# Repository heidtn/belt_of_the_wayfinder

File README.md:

# belt of the wayfinder
This project is the design for a belt that uses vibrational motors to tell the wearer where north is.  This has been inspired by many similar projects in the past.  The basic concept is that by always knowing north, the wearer can gain an intuitive understanding of where north is and improve their sense of direction.

This project includes the PCB design, firmware, and mechanical assemblies.

CAD has been designed using Onshape and the link can be found [here](https://cad.onshape.com/documents/3174cd1b7d359cff45b60529/w/59155bcb796c6976c8cc7d48/e/c52ae8d364edc915756cc2c3)

As of this commit, the firmware and hardware have not yet been tested and development is still underway.

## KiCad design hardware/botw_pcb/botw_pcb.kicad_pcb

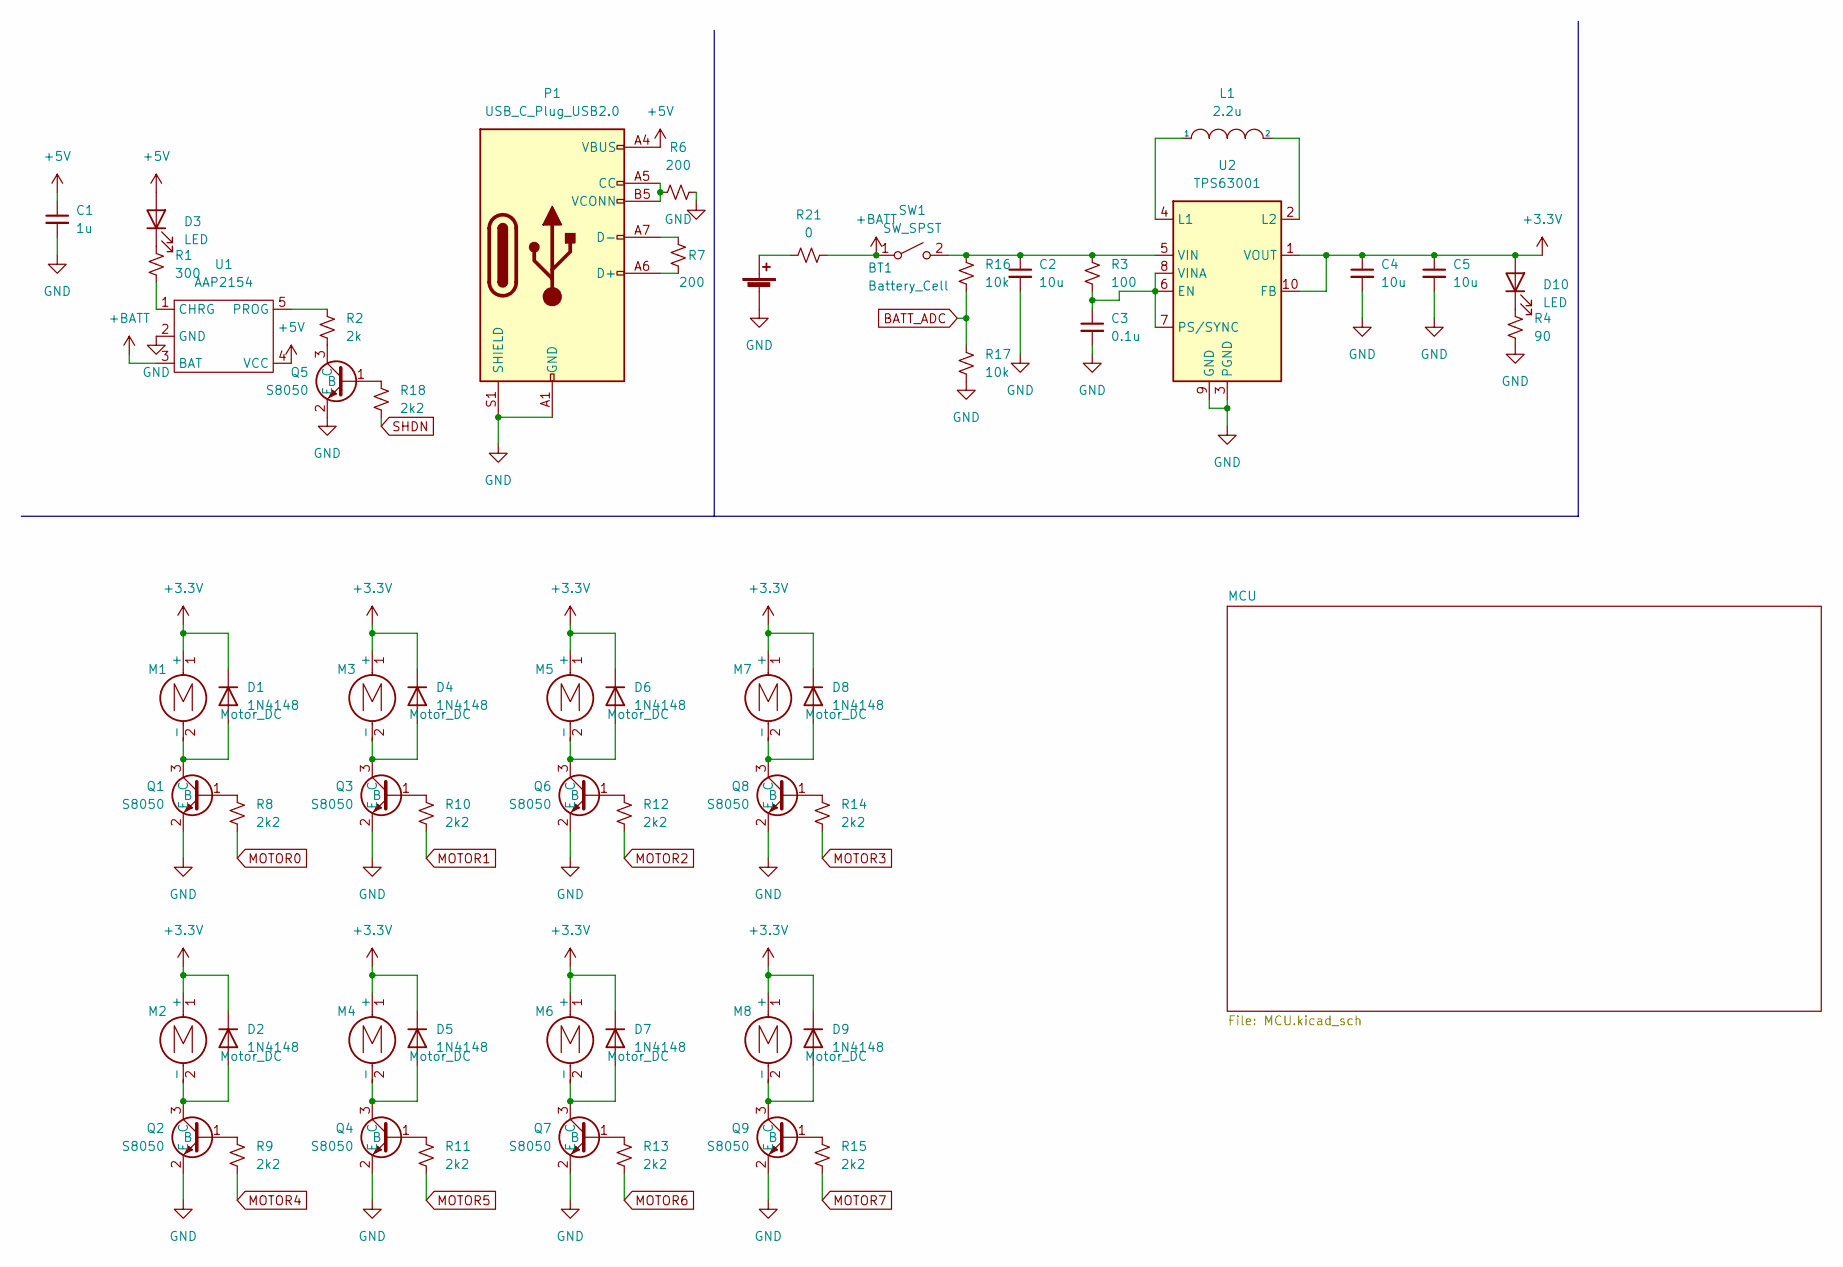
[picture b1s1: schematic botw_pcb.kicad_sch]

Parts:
BT1: Battery_Cell; PinHeader_1x02_P2.54mm_Vertical
C1: 1u; C_0603_1608Metric
C2, C4, C5: 10u; C_0603_1608Metric
C3: 0.1u; C_0603_1608Metric
D1, D2, D4, D5, D6, D7, D8, D9: 1N4148; D_SOD-123
D3, D10: LED; LED_0603_1608Metric
L1: 2.2u; L_0805_2012Metric
M1, M2, M3, M4, M5, M6, M7, M8: Motor_DC; PinHeader_1x02_P2.54mm_Vertical
P1: USB_C_Plug_USB2.0; USB_C_Receptacle_HRO_TYPE-C-31-M-12
Q1, Q2, Q3, Q4, Q5, Q6, Q7, Q8, Q9: S8050; SOT-23
R1: 300; R_0603_1608Metric
R2: 2k; R_0603_1608Metric
R3: 100; R_0603_1608Metric
R4: 90; R_0603_1608Metric
R6, R7: 200; R_0603_1608Metric
R8, R9, R10, R11, R12, R13, R14, R15, R18: 2k2; R_0603_1608Metric
R16, R17: 10k; R_0603_1608Metric
R21: 0; R_0603_1608Metric
SW1: SW_SPST; PinSocket_1x02_P2.54mm_Vertical
U1: AAP2154; TSOT-25
U2: TPS63001; Texas_DRC0010J_ThermalVias

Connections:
+3.3V: C4.1, C5.1, D1.1 (K), D2.1 (K), D4.1 (K), D5.1 (K), D6.1 (K), D7.1 (K), D8.1 (K), D9.1 (K), D10.2 (A), M1.1 (+), M2.1 (+), M3.1 (+), M4.1 (+), M5.1 (+), M6.1 (+), M7.1 (+), M8.1 (+), U2.1 (VOUT), U2.10 (FB); also elsewhere on the board
+5V: C1.1, D3.2 (A), P1.A4 (VBUS), P1.A9 (VBUS), P1.B4 (VBUS), P1.B9 (VBUS), U1.4 (VCC)
+BATT: R21.2, SW1.1 (A), U1.3 (BAT)
BATT_ADC: R16.2, R17.1; also elsewhere on the board
GND: BT1.2 (-), C1.2, C2.2, C3.2, C4.2, C5.2, P1.A1 (GND), P1.A12 (GND), P1.B1 (GND), P1.B12 (GND), P1.S1 (SHIELD), Q1.2 (E), Q2.2 (E), Q3.2 (E), Q4.2 (E), Q5.2 (E), Q6.2 (E), Q7.2 (E), Q8.2 (E), Q9.2 (E), R4.2, R6.2, R17.2, U1.2 (GND), U2.3 (PGND), U2.9 (GND), U2.11 (PGND); also elsewhere on the board
MOTOR0: R8.2; also elsewhere on the board
MOTOR1: R10.2; also elsewhere on the board
MOTOR2: R12.2; also elsewhere on the board
MOTOR3: R14.2; also elsewhere on the board
MOTOR4: R9.2; also elsewhere on the board
MOTOR5: R11.2; also elsewhere on the board
MOTOR6: R13.2; also elsewhere on the board
MOTOR7: R15.2; also elsewhere on the board
unnamed: BT1.1 (+), R21.1
unnamed: C2.1, R3.1, R16.1, SW1.2 (B), U2.5 (VIN)
unnamed: C3.1, R3.2, U2.6 (EN), U2.7 (PS/SYNC), U2.8 (VINA)
unnamed: D1.2 (A), M1.2 (-), Q1.3 (C)
unnamed: D2.2 (A), M2.2 (-), Q2.3 (C)
unnamed: D3.1 (K), R1.1
unnamed: D4.2 (A), M3.2 (-), Q3.3 (C)
unnamed: D5.2 (A), M4.2 (-), Q4.3 (C)
unnamed: D6.2 (A), M5.2 (-), Q6.3 (C)
unnamed: D7.2 (A), M6.2 (-), Q7.3 (C)
unnamed: D8.2 (A), M7.2 (-), Q8.3 (C)
unnamed: D9.2 (A), M8.2 (-), Q9.3 (C)
unnamed: D10.1 (K), R4.1
unnamed: L1.1, U2.4 (L1)
unnamed: L1.2, U2.2 (L2)
unnamed: P1.A5 (CC), P1.B5 (VCONN), R6.1
unnamed: P1.A6 (D+), R7.2
unnamed: P1.A7 (D-), R7.1
unnamed: R1.2, U1.1 (CHRG)
unnamed: R2.1, U1.5 (PROG)
unnamed: Q5.3 (C), R2.2
unnamed: Q1.1 (B), R8.1
unnamed: Q2.1 (B), R9.1
unnamed: Q3.1 (B), R10.1
unnamed: Q4.1 (B), R11.1
unnamed: Q6.1 (B), R12.1
unnamed: Q7.1 (B), R13.1
unnamed: Q8.1 (B), R14.1
unnamed: Q9.1 (B), R15.1
unnamed: Q5.1 (B), R18.1
SHDN: R18.2; also elsewhere on the board

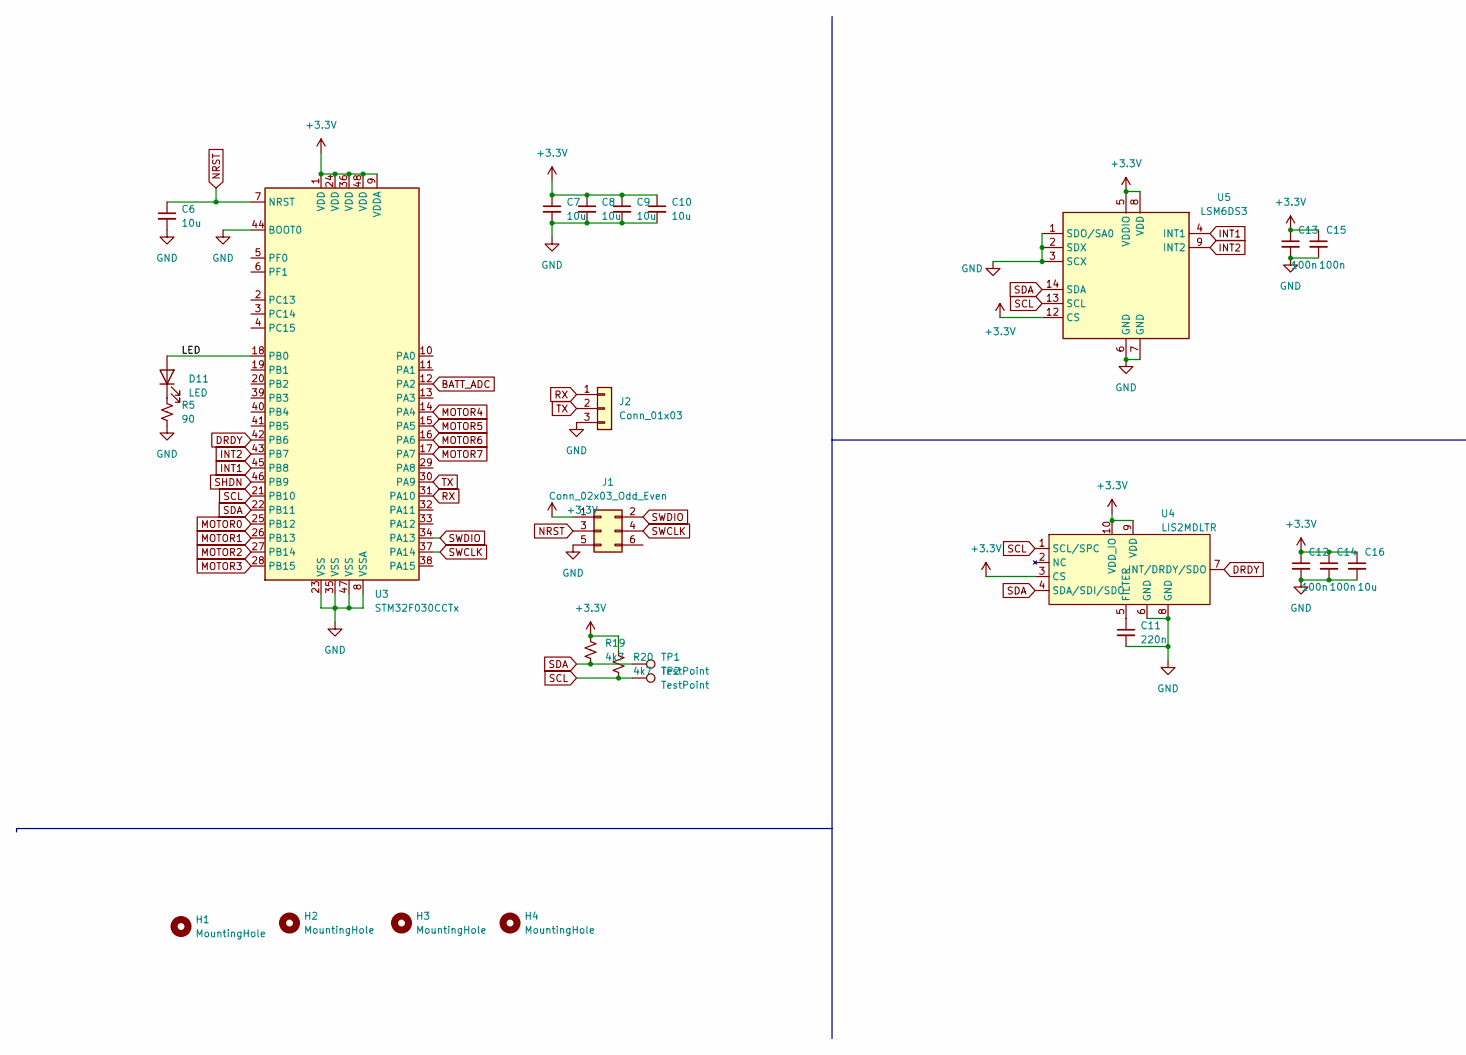
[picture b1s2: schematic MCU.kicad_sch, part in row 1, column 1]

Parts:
C6, C7, C8, C9, C10, C16: 10u; C_0603_1608Metric
C11: 220n; C_0603_1608Metric
C12, C13, C14, C15: 100n; C_0603_1608Metric
D11: LED; LED_0603_1608Metric
H1, H2, H3, H4: MountingHole; MountingHole_2.7mm_M2.5
J1: Conn_02x03_Odd_Even; Tag-Connect_TC2030-IDC-FP_2x03_P1.27mm_Vertical
J2: Conn_01x03; PinHeader_1x03_P2.54mm_Vertical
R5: 90; R_0603_1608Metric
R19, R20: 4k7; R_0603_1608Metric
TP1, TP2: TestPoint; TestPoint_Pad_D1.0mm
U3: STM32F030CCTx; LQFP-48_7x7mm_P0.5mm
U4: LIS2MDLTR; LGA-12_2x2mm_P0.5mm
U5: LSM6DS3; LGA-14_3x2.5mm_P0.5mm_LayoutBorder3x4y

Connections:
+3.3V: C7.1, C8.1, C9.1, C10.1, C12.1, C13.1, C14.1, C15.1, C16.1, J1.1, R19.1, R20.1, U3.1 (VDD), U3.9 (VDDA), U3.24 (VDD), U3.36 (VDD), U3.48 (VDD), U4.3 (CS), U4.9 (VDD), U4.10 (VDD_IO), U5.5 (VDDIO), U5.8 (VDD), U5.12 (CS); also elsewhere on the board
/MCU/LED: D11.2 (A), U3.18 (PB0)
BATT_ADC: U3.12 (PA2); also elsewhere on the board
DRDY: U3.42 (PB6), U4.7 (INT/DRDY/SDO)
GND: C6.2, C7.2, C8.2, C9.2, C10.2, C11.2, C12.2, C13.2, C14.2, C15.2, C16.2, J1.5, J2.3, R5.2, U3.8 (VSSA), U3.23 (VSS), U3.35 (VSS), U3.44 (BOOT0), U3.47 (VSS), U4.6 (GND), U4.8 (GND), U5.1 (SDO/SA0), U5.2 (SDX), U5.3 (SCX), U5.6 (GND), U5.7 (GND); also elsewhere on the board
INT1: U3.45 (PB8), U5.4 (INT1)
INT2: U3.43 (PB7), U5.9 (INT2)
MOTOR0: U3.25 (PB12); also elsewhere on the board
MOTOR1: U3.26 (PB13); also elsewhere on the board
MOTOR2: U3.27 (PB14); also elsewhere on the board
MOTOR3: U3.28 (PB15); also elsewhere on the board
MOTOR4: U3.14 (PA4); also elsewhere on the board
MOTOR5: U3.15 (PA5); also elsewhere on the board
MOTOR6: U3.16 (PA6); also elsewhere on the board
MOTOR7: U3.17 (PA7); also elsewhere on the board
NRST: C6.1, J1.3, U3.7 (NRST)
unnamed: C11.1, U4.5 (FILTER)
unnamed: D11.1 (K), R5.1
RX: J2.1, U3.31 (PA10)
SCL: R20.2, TP2.1, U3.21 (PB10), U4.1 (SCL/SPC), U5.13 (SCL)
SDA: R19.2, TP1.1, U3.22 (PB11), U4.4 (SDA/SDI/SDO), U5.14 (SDA)
SHDN: U3.46 (PB9); also elsewhere on the board
SWCLK: J1.4, U3.37 (PA14)
SWDIO: J1.2, U3.34 (PA13)
TX: J2.2, U3.30 (PA9)

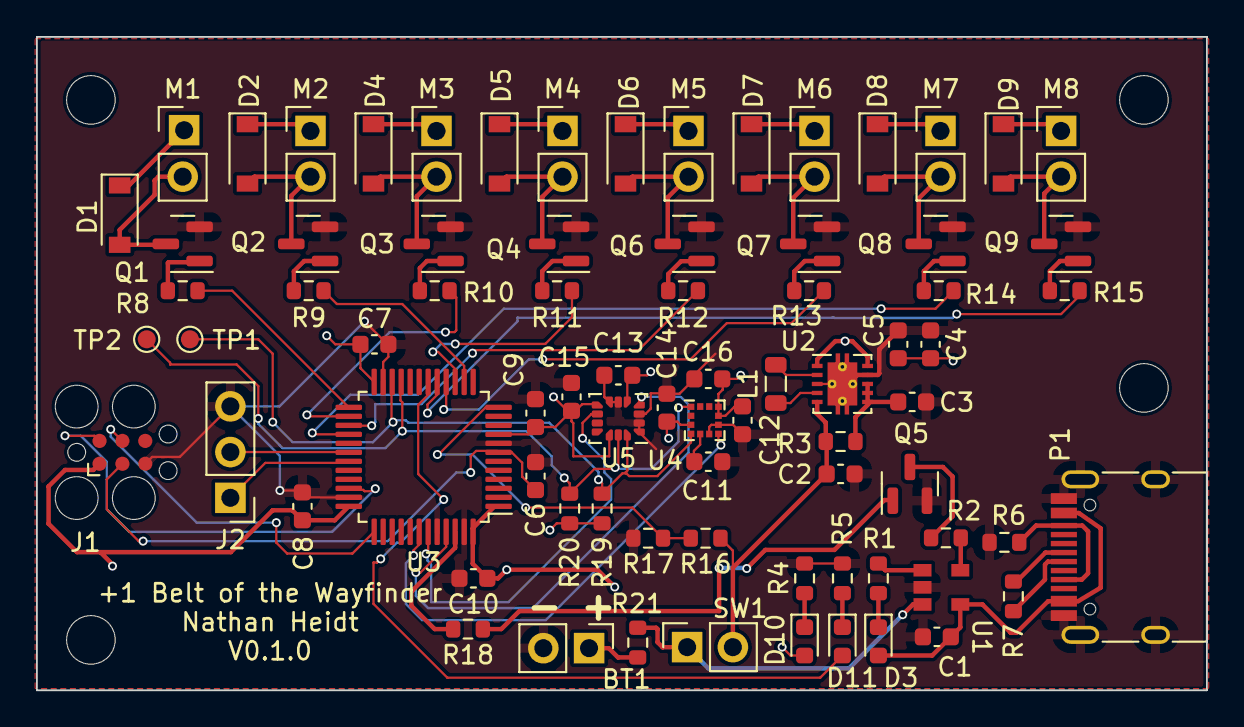
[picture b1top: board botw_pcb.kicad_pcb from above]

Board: 2 copper layers, 65.0 x 36.3 mm, 82 parts (0 on the bottom side), 57 nets.

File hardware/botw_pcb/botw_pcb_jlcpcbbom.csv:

Value,Reference(s),Footprint,JLCPCB Part #
1u,C1,Capacitor_SMD:C_0603_1608Metric,C15849
10u,"C2, C4, C5, C6, C7, C8, C9, C10, C16",Capacitor_SMD:C_0603_1608Metric,C19702
0.1u,C3,Capacitor_SMD:C_0603_1608Metric,C14663
220n,C11,Capacitor_SMD:C_0603_1608Metric,C21120
100n,"C12, C13, C14, C15",Capacitor_SMD:C_0603_1608Metric,C14663
1N4148,"D1, D2, D4, D5, D6, D7, D8, D9",Diode_SMD:D_SOD-123,C81598
LED,D3,LED_SMD:LED_0603_1608Metric,C165982
LED,D10,LED_SMD:LED_0603_1608Metric,C138547
LED,D11,LED_SMD:LED_0603_1608Metric,C138545
2.2u,L1,Inductor_SMD:L_0805_2012Metric,C1043
USB_C_Plug_USB2.0,P1,Connector_USB:USB_C_Receptacle_HRO_TYPE-C-31-M-12,C165948
S8050,"Q1, Q2, Q3, Q4, Q5, Q6, Q7, Q8, Q9",Package_TO_SOT_SMD:SOT-23,C2146
300,"R1, R4",Resistor_SMD:R_0603_1608Metric,C23025
2k,R2,Resistor_SMD:R_0603_1608Metric,C22975
100,"R3, R5",Resistor_SMD:R_0603_1608Metric,C22775
200,"R6, R7",Resistor_SMD:R_0603_1608Metric,C8218
2k2,"R8, R9, R10, R11, R12, R13, R14, R15, R18",Resistor_SMD:R_0603_1608Metric,C4190
10k,"R16, R17",Resistor_SMD:R_0603_1608Metric,C25804
4k7,"R19, R20",Resistor_SMD:R_0603_1608Metric,C23162
AAP2154,U1,custom_footprints:TSOT-25,C370749
TPS63001,U2,Package_SON:Texas_DRC0010J_ThermalVias,C28060
STM32F030CCTx,U3,Package_QFP:LQFP-48_7x7mm_P0.5mm,C81787
LIS2MDLTR,U4,Package_LGA:LGA-12_2x2mm_P0.5mm,C919695
LSM6DS3,U5,Package_LGA:LGA-14_3x2.5mm_P0.5mm_LayoutBorder3x4y,C967633

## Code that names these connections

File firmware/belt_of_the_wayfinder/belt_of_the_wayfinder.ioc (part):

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PB13.GPIOParameters=GPIO_Speed,PinState,GPIO_PuPd,GPIO_Label
Mcu.UserName=STM32F030CCTx
PB10.Mode=I2C
PB14.GPIO_Label=MOTOR2
PA6.GPIO_Label=MOTOR6
PB13.GPIO_Label=MOTOR1
PB11.Signal=I2C2_SDA
PB13.Signal=GPIO_Output
PB15.Signal=GPIO_Output
PA5.PinState=GPIO_PIN_RESET
PB15.PinState=GPIO_PIN_RESET
RCC.SYSCLKSource=RCC_SYSCLKSOURCE_PLLCLK
PB11.GPIO_Speed=GPIO_SPEED_FREQ_HIGH
PA7.PinState=GPIO_PIN_RESET
PB12.PinState=GPIO_PIN_RESET
PA4.GPIO_PuPd=GPIO_PULLDOWN
PA4.GPIO_Speed=GPIO_SPEED_FREQ_MEDIUM
PB12.GPIO_Label=MOTOR0
PA6.GPIO_PuPd=GPIO_PULLDOWN
PA14.Mode=Serial_Wire
PA5.GPIO_PuPd=GPIO_PULLDOWN
PA0.Signal=GPXTI0
PB9.Signal=GPIO_Output
Mcu.Package=LQFP48
PB14.GPIO_PuPd=GPIO_PULLDOWN
PA6.Signal=GPIO_Output
PB15.GPIO_PuPd=GPIO_PULLDOWN
PA10.Signal=USART1_RX
PB9.GPIO_PuPd=GPIO_PULLDOWN
PA5.GPIOParameters=GPIO_Speed,PinState,GPIO_PuPd,GPIO_Label
PB14.GPIOParameters=GPIO_Speed,PinState,GPIO_PuPd,GPIO_Label
PA6.GPIO_Speed=GPIO_SPEED_FREQ_MEDIUM
PB11.GPIO_Mode=GPIO_MODE_AF_OD
PA4.GPIO_Label=MOTOR4
PA6.GPIOParameters=GPIO_Speed,PinState,GPIO_PuPd,GPIO_Label
PB9.GPIO_Label=SHDN
PA10.Mode=Asynchronous
PB11.GPIO_PuPdOD=GPIO_PULLUP
PA6.PinState=GPIO_PIN_RESET
PB9.GPIOParameters=GPIO_PuPd,GPIO_Label
PA13.Signal=SYS_SWDIO
PA9.Mode=Asynchronous
PB14.PinState=GPIO_PIN_RESET
PA4.PinState=GPIO_PIN_RESET
PB11.Mode=I2C
PB14.GPIO_Speed=GPIO_SPEED_FREQ_MEDIUM
PA9.Signal=USART1_TX
PB13.GPIO_Speed=GPIO_SPEED_FREQ_MEDIUM
PB11.GPIOParameters=GPIO_Speed,GPIO_PuPdOD,GPIO_Mode
PA7.GPIO_PuPd=GPIO_PULLDOWN
PA1.Signal=GPXTI1
PB12.GPIO_Speed=GPIO_SPEED_FREQ_MEDIUM
PB10.Signal=I2C2_SCL
PB14.Signal=GPIO_Output
PA5.Signal=GPIO_Output
board=custom
PA7.GPIO_Speed=GPIO_SPEED_FREQ_MEDIUM
PB13.GPIO_PuPd=GPIO_PULLDOWN
PB13.PinState=GPIO_PIN_RESET
PB15.GPIO_Label=MOTOR3
PB15.GPIO_Speed=GPIO_SPEED_FREQ_MEDIUM
PA4.GPIOParameters=GPIO_Speed,PinState,GPIO_PuPd,GPIO_Label
PB15.GPIOParameters=GPIO_Speed,PinState,GPIO_PuPd,GPIO_Label
PA13.Mode=Serial_Wire
Mcu.Name=STM32F030CCTx
PA2.Signal=ADC_IN2
PA4.Signal=GPIO_Output
RCC.SYSCLKFreq_VALUE=48000000
PA7.GPIO_Label=MOTOR7
PA5.GPIO_Label=MOTOR5
PA14.Signal=SYS_SWCLK
PA5.GPIO_Speed=GPIO_SPEED_FREQ_MEDIUM
PA2.Mode=IN2
PB8.Signal=GPXTI8
PB12.GPIO_PuPd=GPIO_PULLDOWN
PB0.Signal=GPIO_Output
PA7.GPIOParameters=GPIO_Speed,PinState,GPIO_PuPd,GPIO_Label
PB12.GPIOParameters=GPIO_Speed,PinState,GPIO_PuPd,GPIO_Label
PB12.Signal=GPIO_Output
PA7.Signal=GPIO_Output

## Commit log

2022-11-17 Initial commit, basic belt design and firmware
2022-12-04 Added pullups to I2C'
2022-12-06 Changed to a new part for mag
2022-12-16 Transistor footprint was wrong, whoops! Also added in hard iron correction
2022-12-16 Hard iron correction in firmware and early work on other features
